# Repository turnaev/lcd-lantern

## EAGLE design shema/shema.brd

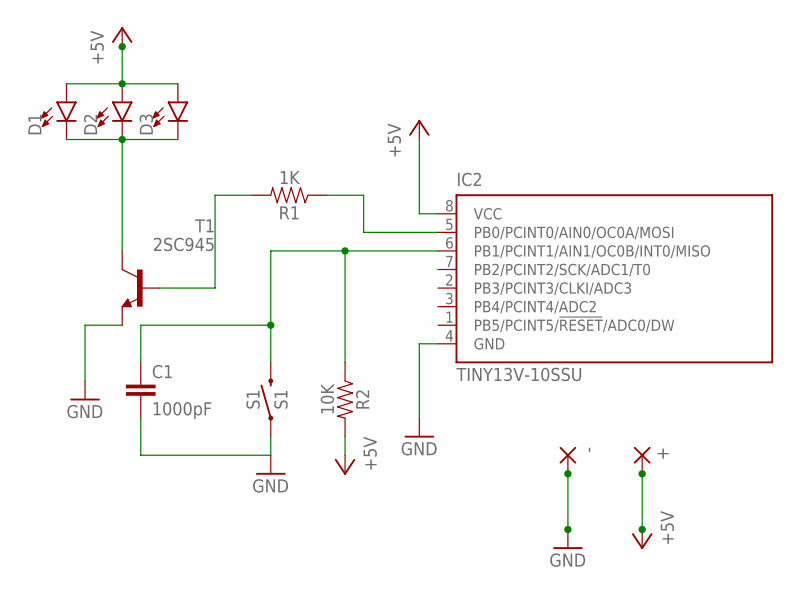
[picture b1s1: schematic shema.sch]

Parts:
+: 2,54/0,8
-: 2,54/0,8
C1: 1000pF; 0603
D1, D2, D3: LED-3MM-NO_SILK; LED_3MM-NS
IC2: TINY13V-10SSU; 8S1
R1: 1K; 0603
R2: 10K; 0603
S1: S1; TACTILE_SWITCH_SMD_4.5MM
T1: 2SC945; TO92-ECB

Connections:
+5V: +.1, D1.A, D2.A, D3.A, IC2.8 (VCC), R2.2
GND: -.1, C1.2, IC2.4 (GND), S1.2 (1), S1.3 (1), T1.E
unnamed: IC2.5 (PB0/PCINT0/AIN0/OC0A/MOSI), R1.1
unnamed: C1.1, IC2.6 (PB1/PCINT1/AIN1/OC0B/INT0/MISO), R2.1, S1.1 (2), S1.4 (2)
unnamed: R1.2, T1.B
unnamed: D1.K (C), D2.K (C), D3.K (C), T1.C

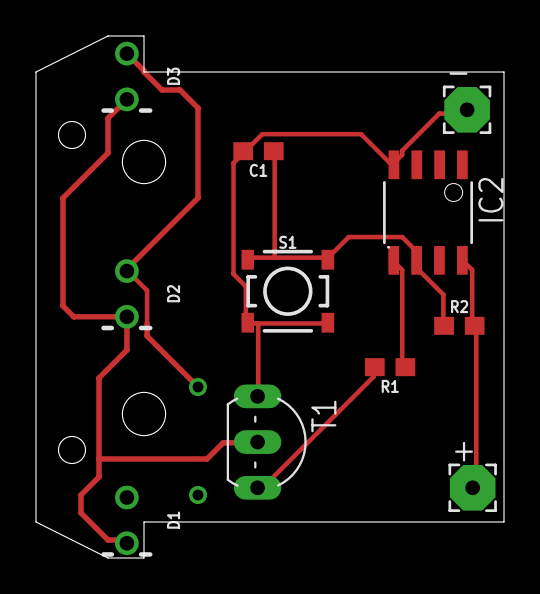
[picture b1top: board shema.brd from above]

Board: 2 copper layers, 26.0 x 29.0 mm, 11 parts (0 on the bottom side), 6 nets.

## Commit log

2017-08-14 init
2017-08-15 add soft
2017-08-22 soft
2017-08-22 tabs to spaces
2017-08-28 remove history files
2017-08-28 git ignore history

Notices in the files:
parts and their libraries:
SparkFun-Capacitors: Licensing: Creative Commons ShareAlike 4.0 International - https://creativecommons.org/licenses/by-sa/4.0
